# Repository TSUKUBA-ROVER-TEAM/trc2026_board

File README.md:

# trc2026_board
鳥取ローバーチャレンジ2026 基板設計リポジトリ

### 開発環境
- KiCad 9.0.4

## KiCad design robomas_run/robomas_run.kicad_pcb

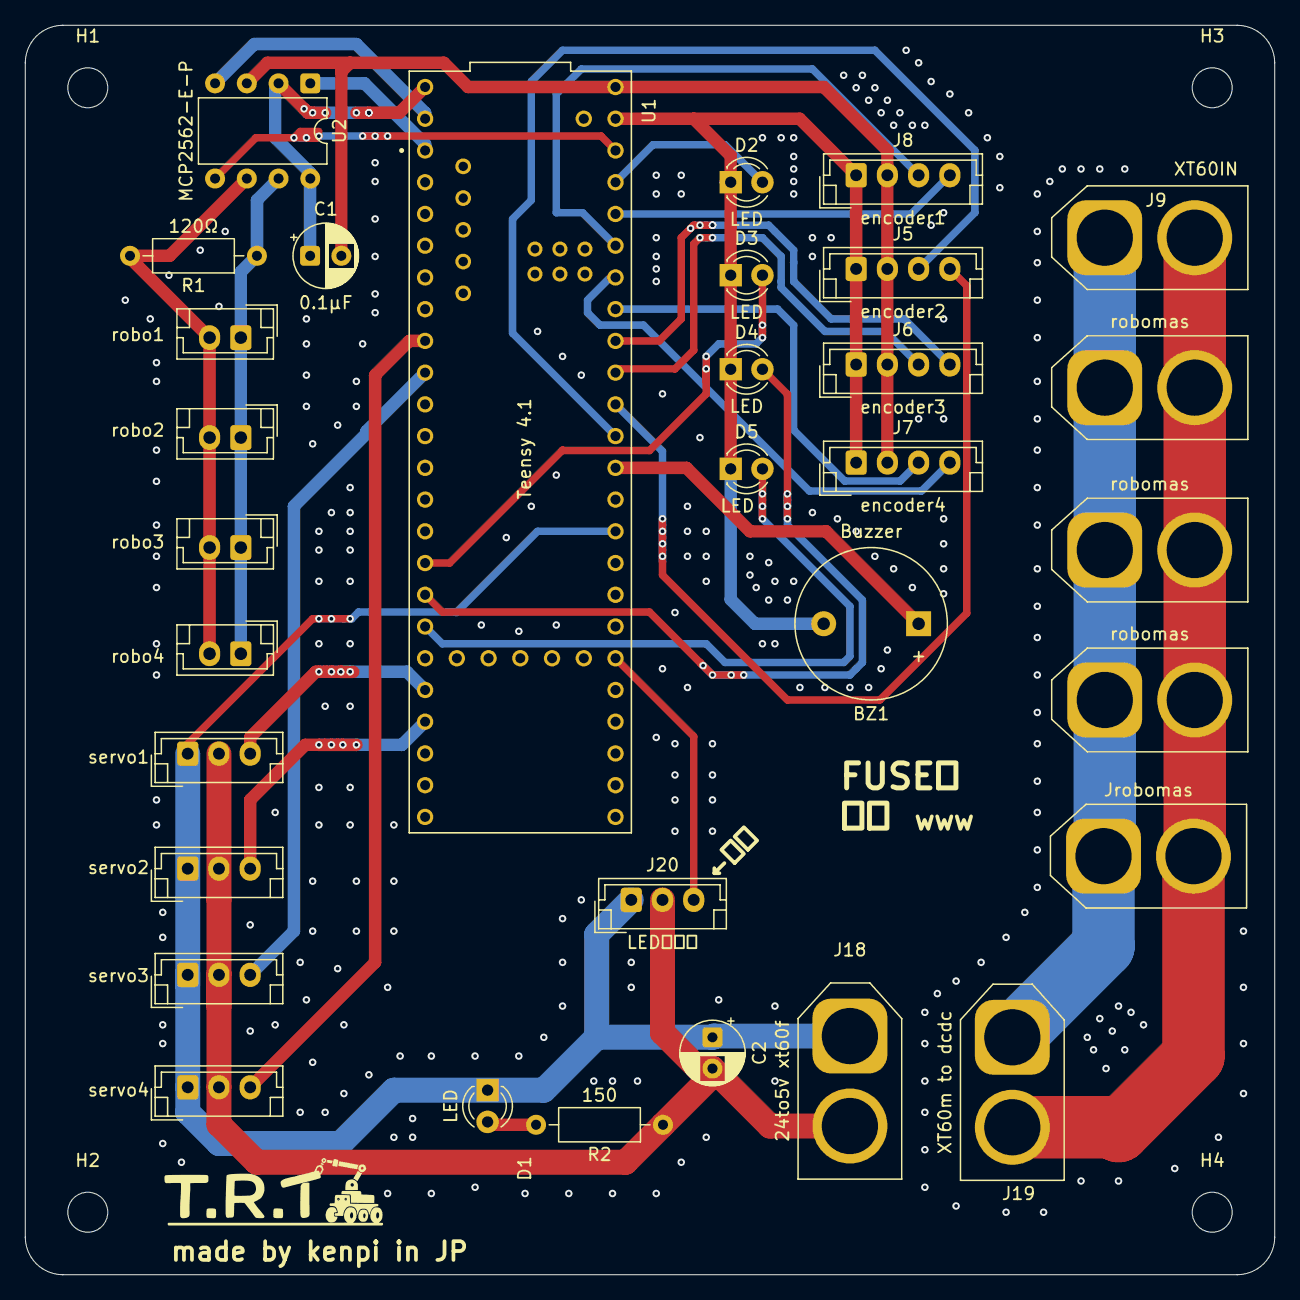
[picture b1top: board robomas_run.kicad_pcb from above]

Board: 2 copper layers, 100.0 x 100.0 mm, 36 parts (0 on the bottom side), 30 nets.

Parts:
BZ1: Buzzer; Buzzer_12x9.5RM7.6
C1: 0.1μF; CP_Radial_D5.0mm_P2.50mm
C2: C; CP_Radial_D5.0mm_P2.50mm
D1, D2, D3, D4, D5: LED; LED_D3.0mm
H1, H2, H3, H4: MountingHole; MountingHole_3.2mm_M3
J5: encoder2; JST_EH_B4B-EH-A_1x04_P2.50mm_Vertical
J6: encoder3; JST_EH_B4B-EH-A_1x04_P2.50mm_Vertical
J7: encoder4; JST_EH_B4B-EH-A_1x04_P2.50mm_Vertical
J8: encoder1; JST_EH_B4B-EH-A_1x04_P2.50mm_Vertical
J9: XT60IN; AMASS_XT60-F_1x02_P7.20mm_Vertical
J18: 24to5v xt60f; AMASS_XT60-F_1x02_P7.20mm_Vertical
J19: XT60m to dcdc; AMASS_XT60-M_1x02_P7.20mm_Vertical
J20: LEDテープ; JST_EH_B3B-EH-A_1x03_P2.50mm_Vertical
Jrobomas: XT30; AMASS_XT60-M_1x02_P7.20mm_Vertical
R1: 120Ω; R_Axial_DIN0207_L6.3mm_D2.5mm_P10.16mm_Horizontal
R2: 150; R_Axial_DIN0207_L6.3mm_D2.5mm_P10.16mm_Horizontal
U1: DEV-16771; MODULE_DEV-16771
U2: MCP2562-E-P; DIP-8_W7.62mm
robo1, robo2, robo3, robo4: Conn_01x02_Pin; JST_EH_B2B-EH-A_1x02_P2.50mm_Vertical
robomas: XT30; AMASS_XT60-M_1x02_P7.20mm_Vertical
robomas#2, robomas#3: XT30; AMASS_XT60-M_1x02_P7.20mm_Vertical
servo1, servo2, servo3, servo4: XA; JST_EH_B3B-EH-A_1x03_P2.50mm_Vertical

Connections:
3.3V: U1.3.3V_1 (3.3V), U1.3.3V_2 (3.3V), U1.3.3V_3 (3.3V), U2.5 (Vio)
+5V: C2.2, J18.2, J20.2, R2.1, servo1.2, servo2.2, servo3.2, servo4.2
+24V: J9.2, J19.2, Jrobomas.2, robomas.2, robomas#2.2, robomas#3.2
-5V: BZ1.2 (-), C1.1, C2.1, D1.1 (K), D2.1 (K), D3.1 (K), D4.1 (K), D5.1 (K), J5.1, J6.1, J7.1, J8.1, J18.1, J20.1, U1.GND1 (GND), U1.GND2 (GND), U1.GND3 (GND), U1.GND4 (GND), U1.GND5 (GND), U2.2 (VSS), U2.8 (STBY), servo1.1, servo2.1, servo3.1, servo4.1
unnamed: BZ1.1 (+), U1.14 (A0)
unnamed: D1.2 (A), R2.2
unnamed: D2.2 (A), U1.23 (A9)
unnamed: D3.2 (A), U1.24 (A10)
unnamed: D4.2 (A), U1.25 (A11)
unnamed: D5.2 (A), U1.26 (A12)
unnamed: R1.1, U2.7 (CANH), robo1.1, robo2.1, robo3.1, robo4.1
unnamed: R1.2, U2.6 (CANL), robo1.2, robo2.2, robo3.2, robo4.2
unnamed: C1.2, J5.2, J6.2, J7.2, J8.2, U1.VIN, U2.3 (VDD)
unnamed: J5.3, U1.15 (A1)
unnamed: J5.4, U1.16 (A2)
unnamed: J6.3, U1.17 (A3)
unnamed: J6.4, U1.18 (A4)
unnamed: J7.3, U1.19 (A5)
unnamed: J7.4, U1.20 (A6)
unnamed: J8.3, U1.21 (A7)
unnamed: J8.4, U1.22 (A8)
unnamed: J9.1, J19.1, Jrobomas.1, robomas.1, robomas#2.1, robomas#3.1
unnamed: U1.28 (RX7), servo1.3
unnamed: U1.29 (TX7), servo2.3
unnamed: U1.8 (TX2), servo3.3
unnamed: U1.7 (RX2), servo4.3
unnamed: J20.3, U1.38 (A14)
unnamed: U1.0 (RX1), U2.4 (RXD)
unnamed: U1.1 (TX1), U2.1 (TXD)
USB_GND: U1.USB_GND1 (USB_GND), U1.USB_GND2 (USB_GND)

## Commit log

2025-09-03 chore: add .gitignore
2025-09-03 docs: specify kicad version
2025-10-16 TeensyのGPS,地磁気周りの回路図を作った。
2025-10-16 位置情報系の回路図の作成をした。
2025-12-07 Add files via upload
    i upload kicad file of robomaster motor control board.
2025-12-11 fix: delete zip and add robomas kicad project
2025-12-11 fix: delete zip
